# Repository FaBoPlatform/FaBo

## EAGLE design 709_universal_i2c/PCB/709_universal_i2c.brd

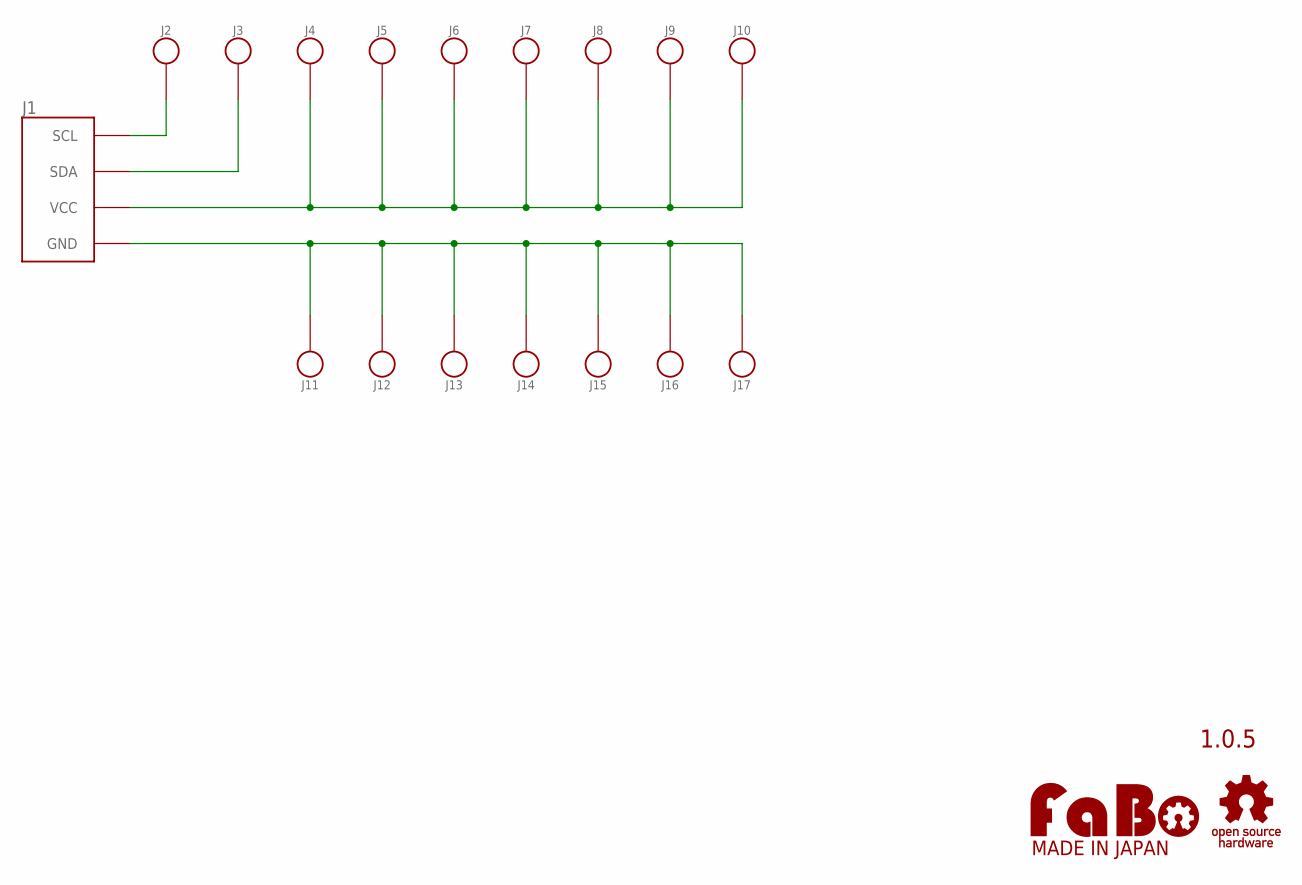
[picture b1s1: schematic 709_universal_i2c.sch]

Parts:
J1: FABO_BRICK_I2C-UNIVERSAL; FABO_BRICK_I2C_UNIVERSAL
J2, J3, J4, J5, J6, J7, J8, J9, J10, J11, J12, J13, J14, J15, J16, J17: PIN_HEADER_1X1_NOLABEL; PIN_1X1_NOLABEL
U$2: LOGO_OSHW-M_BOTTOM; LOGO_OSHW_M_BOTTOM
U$17: LOGO_FABO-M_BOTTOM; LOGO_FABO_MS_BOTTOM

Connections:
GND: J1.GND, J11.1, J12.1, J13.1, J14.1, J15.1, J16.1, J17.1
SCL: J1.SCL, J2.1
SDA: J1.SDA, J3.1
VCC: J1.VCC, J4.1, J5.1, J6.1, J7.1, J8.1, J9.1, J10.1

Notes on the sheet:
1.0.5

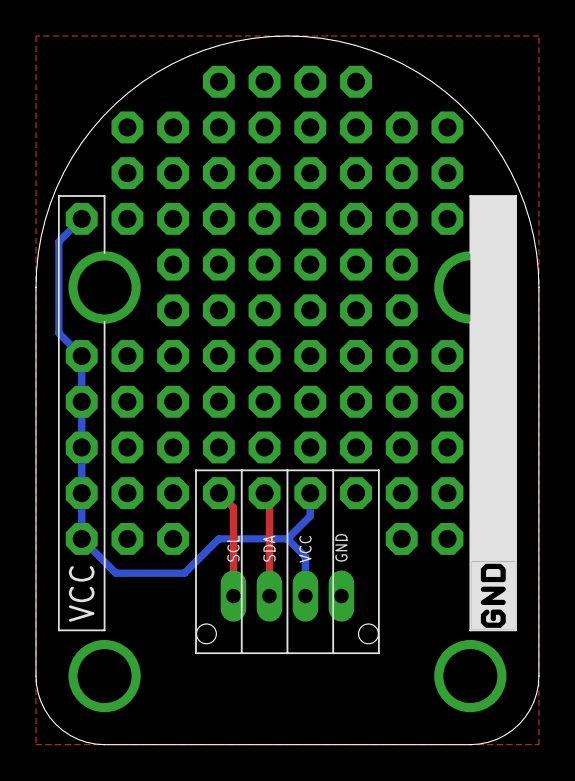
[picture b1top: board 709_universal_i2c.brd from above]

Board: 2 copper layers, 27.9 x 39.4 mm, 20 parts (0 on the bottom side), 4 nets.

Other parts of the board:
U$3: LOGO_SILK_GND

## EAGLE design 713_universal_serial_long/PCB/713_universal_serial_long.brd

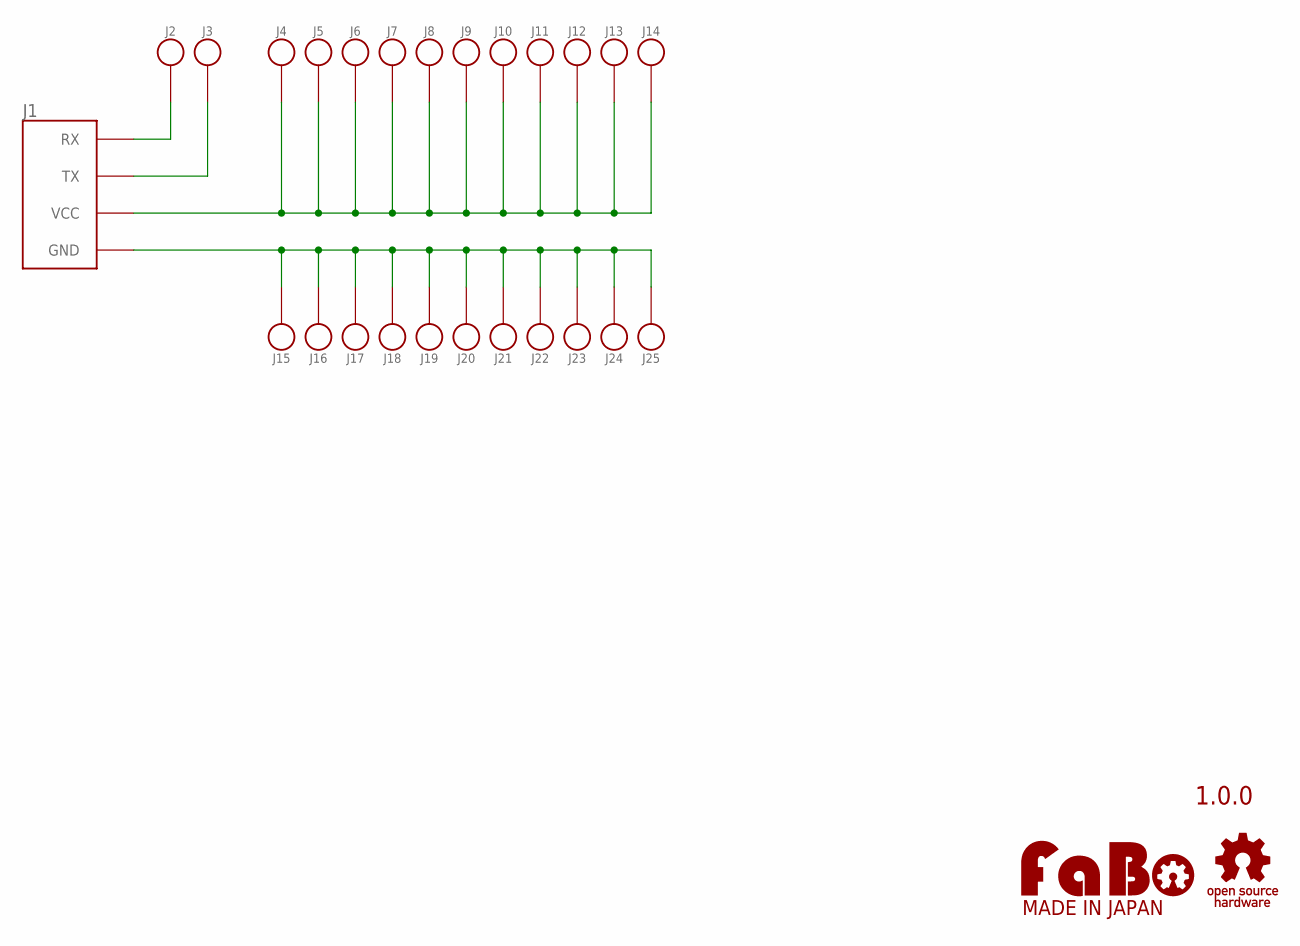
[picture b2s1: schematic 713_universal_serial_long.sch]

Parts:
J1: FABO_BRICK_SERIAL-UNIVERSAL_LONG; FABO_BRICK_SERIAL_UNIVERSAL_LONG
J2, J3, J4, J5, J6, J7, J8, J9, J10, J11, J12, J13, J14, J15, J16, J17, J18, J19, J20, J21, J22, J23, J24, J25: PIN_HEADER_1X1_NOLABEL; PIN_1X1_NOLABEL
U$2: LOGO_OSHW-M_BOTTOM; LOGO_OSHW_M_BOTTOM
U$3: LOGO_FABO-M; LOGO_FABO_MS

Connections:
GND: J1.GND, J15.1, J16.1, J17.1, J18.1, J19.1, J20.1, J21.1, J22.1, J23.1, J24.1, J25.1
RX: J1.RX, J2.1
TX: J1.TX, J3.1
VCC: J1.VCC, J4.1, J5.1, J6.1, J7.1, J8.1, J9.1, J10.1, J11.1, J12.1, J13.1, J14.1

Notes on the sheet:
1.0.0

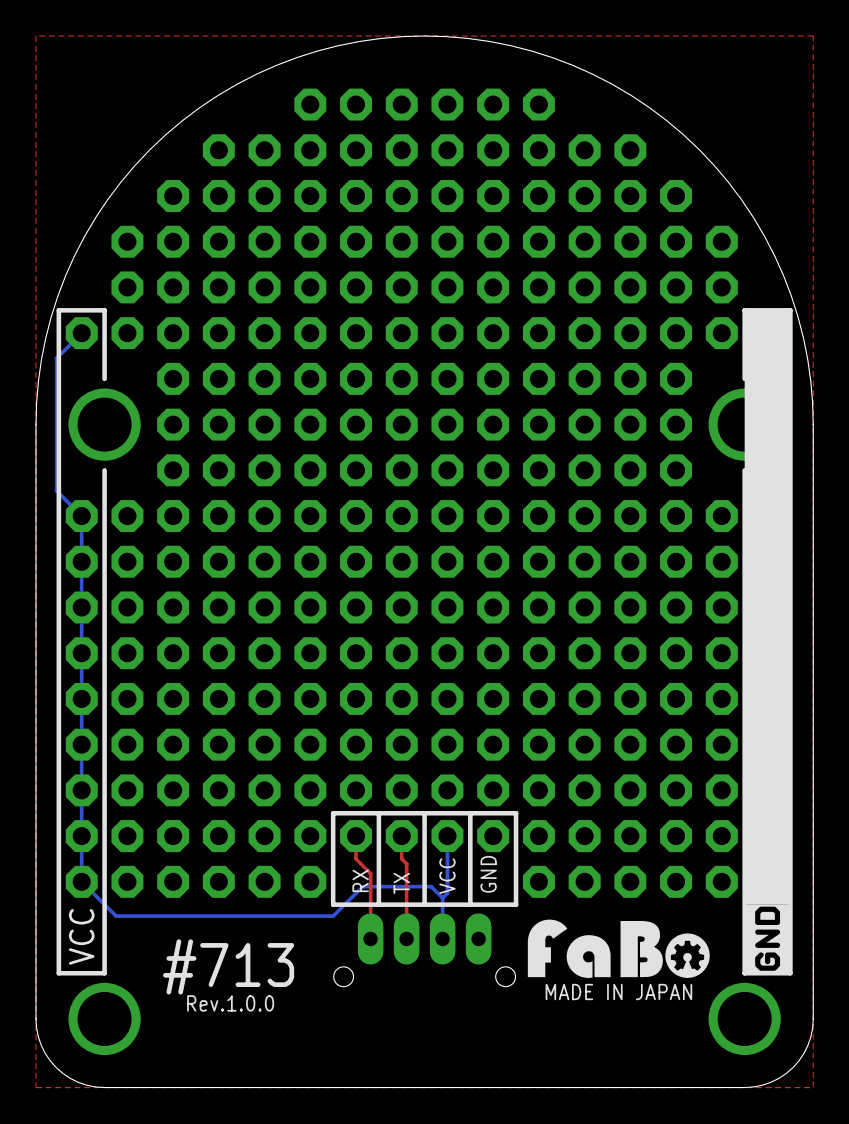
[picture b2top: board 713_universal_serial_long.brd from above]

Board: 2 copper layers, 43.2 x 58.4 mm, 28 parts (0 on the bottom side), 4 nets.

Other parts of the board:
U$4: LOGO_SILK_GND

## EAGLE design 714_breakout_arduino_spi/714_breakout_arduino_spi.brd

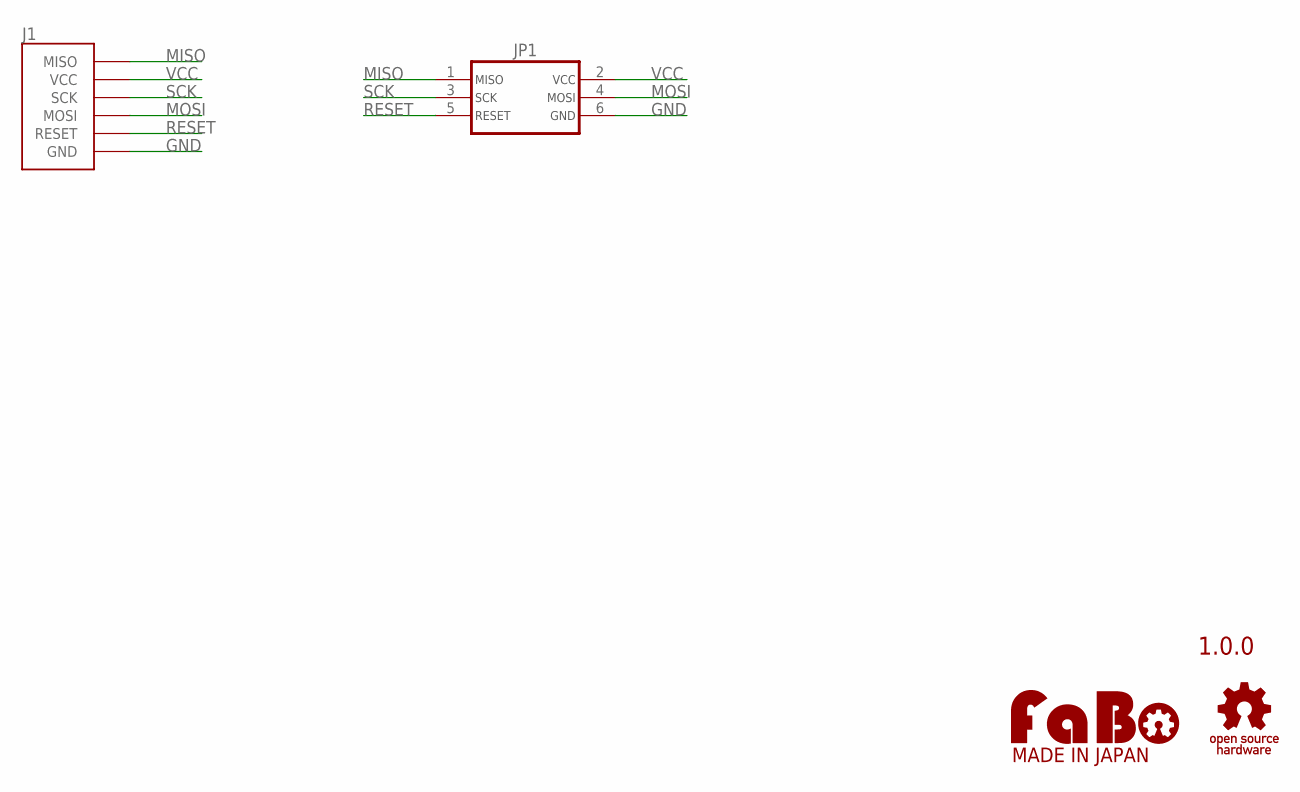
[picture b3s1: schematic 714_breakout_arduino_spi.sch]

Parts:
J1: FABO_BREAKOUT_ARDUINO_SPI
JP1: AVR_ISP-PTH; PIN_2X3
U$2: LOGO_OSHW-M_BOTTOM; LOGO_OSHW_M_BOTTOM
U$3: LOGO_FABO-M_BOTTOM; LOGO_FABO_MS_BOTTOM

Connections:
GND: J1.GND, JP1.6
MISO: J1.MISO, JP1.1
MOSI: J1.MOSI, JP1.4
RESET: J1.RESET, JP1.5
SCK: J1.SCK, JP1.3
VCC: J1.VCC, JP1.2

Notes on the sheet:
1.0.0

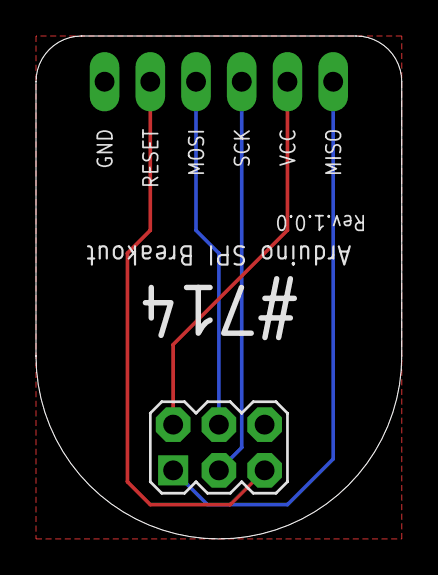
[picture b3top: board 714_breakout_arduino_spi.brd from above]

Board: 2 copper layers, 20.3 x 27.9 mm, 4 parts (0 on the bottom side), 6 nets.

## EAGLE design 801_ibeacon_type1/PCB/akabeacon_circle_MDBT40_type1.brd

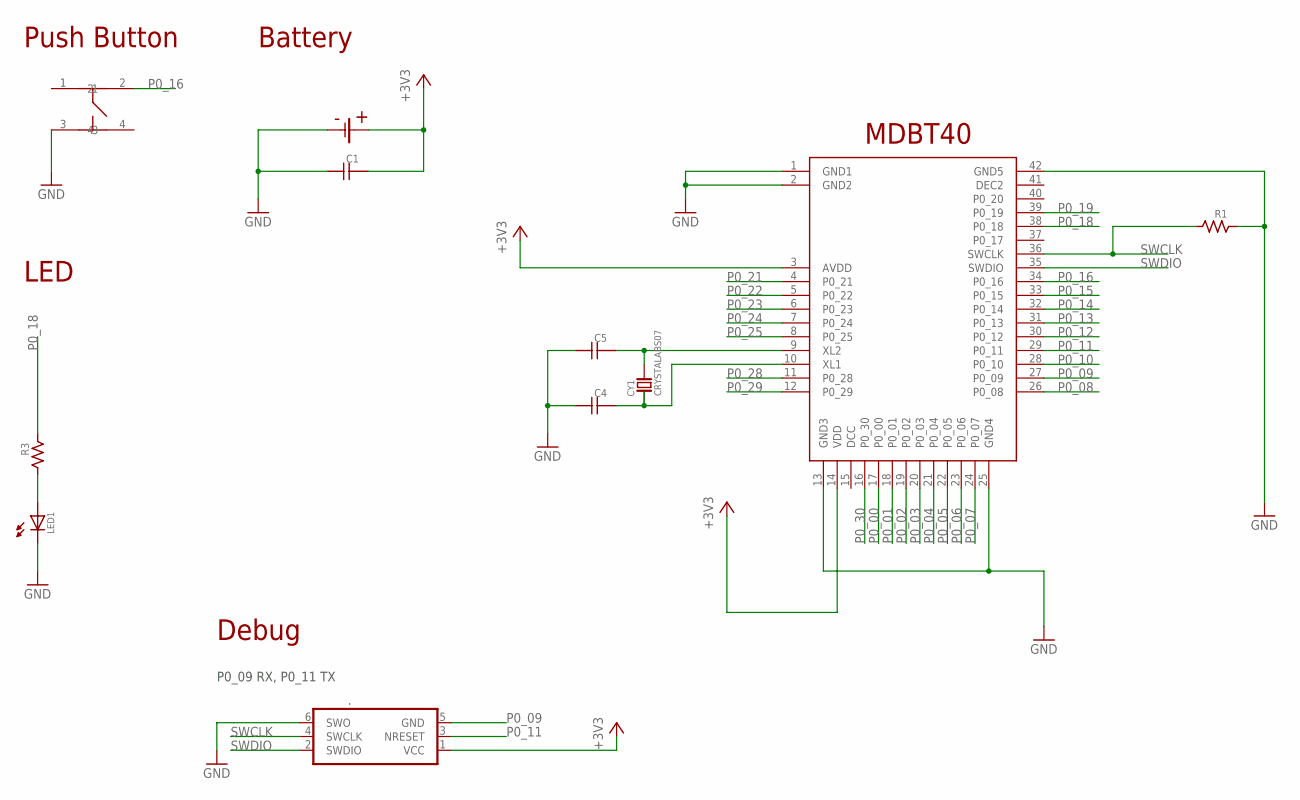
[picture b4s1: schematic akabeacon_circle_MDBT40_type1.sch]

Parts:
.: TC2030-IDC-NL
C1, C4, C5: CAPACITOR-0603; 0603
CY1: CRYSTALABS07; ABRACOM-ABS07-32.768KHZ
LED1: LED-0603; 0603
R1, R3: RESISTOR-0603; 0603
U$1: RAYTAC-MDBT40
U$2: CH031-2477LF
U$5: SWICTH-4P(KMR2); SWITCH-4P(KMR2)

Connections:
+3V3: ..1 (VCC), C1.2, U$1.3 (AVDD), U$1.14 (VDD), U$2.+
GND: ..6 (SWO), C1.1, C4.1, C5.1, LED1.CATHODE, R1.2, U$1.1 (GND1), U$1.2 (GND2), U$1.13 (GND3), U$1.25 (GND4), U$1.42 (GND5), U$2.-, U$5.3
unnamed: LED1.ANODE, R3.1
unnamed: C5.2, CY1.P$2, U$1.9 (XL2)
unnamed: C4.2, CY1.P$1, U$1.10 (XL1)
P0_00: U$1.17 (P0_00)
P0_01: U$1.18 (P0_01)
P0_02: U$1.19 (P0_02)
P0_03: U$1.20 (P0_03)
P0_04: U$1.21 (P0_04)
P0_05: U$1.22 (P0_05)
P0_06: U$1.23 (P0_06)
P0_07: U$1.24 (P0_07)
P0_08: U$1.26 (P0_08)
P0_09: ..5 (GND), U$1.27 (P0_09)
P0_10: U$1.28 (P0_10)
P0_11: ..3 (NRESET), U$1.29 (P0_11)
P0_12: U$1.30 (P0_12)
P0_13: U$1.31 (P0_13)
P0_14: U$1.32 (P0_14)
P0_15: U$1.33 (P0_15)
P0_16: U$1.34 (P0_16), U$5.2
P0_18: R3.2, U$1.38 (P0_18)
P0_19: U$1.39 (P0_19)
P0_21: U$1.4 (P0_21)
P0_22: U$1.5 (P0_22)
P0_23: U$1.6 (P0_23)
P0_24: U$1.7 (P0_24)
P0_25: U$1.8 (P0_25)
P0_28: U$1.11 (P0_28)
P0_29: U$1.12 (P0_29)
P0_30: U$1.16 (P0_30)
SWCLK: ..4 (SWCLK), R1.1, U$1.36 (SWCLK)
SWDIO: ..2 (SWDIO), U$1.35 (SWDIO)

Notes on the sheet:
Battery
Push Button
MDBT40
LED
Debug
P0_09 RX, P0_11 TX

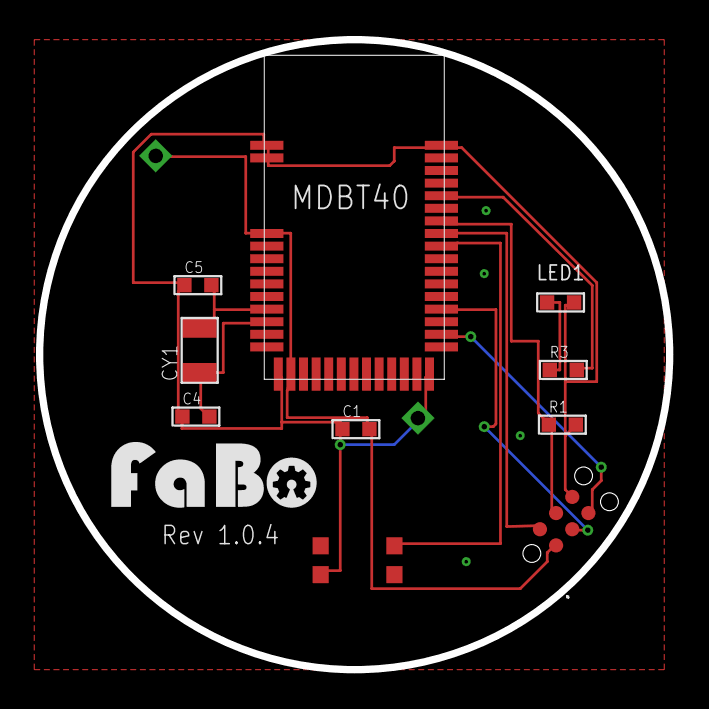
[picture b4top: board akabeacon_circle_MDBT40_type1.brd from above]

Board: 2 copper layers, 35.0 x 35.0 mm, 12 parts (0 on the bottom side), 11 nets.

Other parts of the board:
U$3: LOGO_FABO_M

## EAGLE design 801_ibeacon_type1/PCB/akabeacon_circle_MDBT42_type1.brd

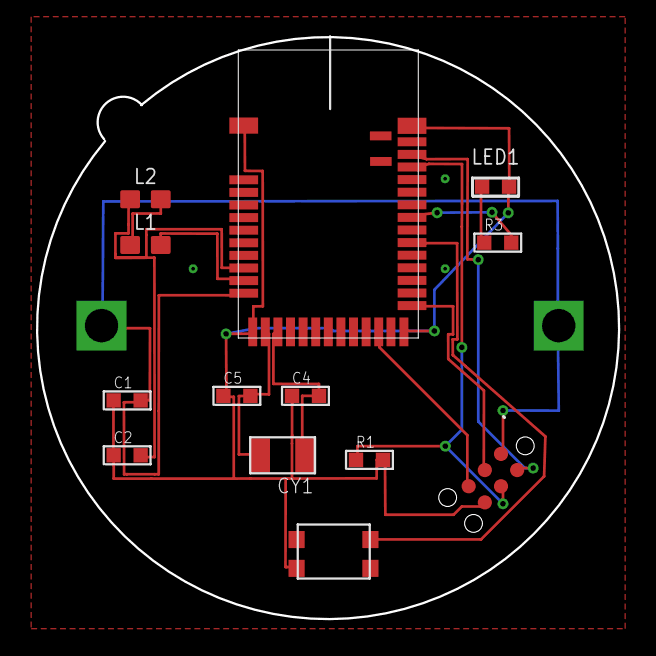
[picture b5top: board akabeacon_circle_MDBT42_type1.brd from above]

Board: 2 copper layers, 32.3 x 32.3 mm, 14 parts (0 on the bottom side), 14 nets.

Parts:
.: TC2030-IDC-NL
C1: 0603
C2: 1uf; 0603
C4: 12@f; 0603
C5: 12pf; 0603
CY1: CRYSTALABS07; ABRACOM-ABS07-32.768KHZ
L1: 10nh; 0603
L2: 15nh; 0603
LED1: 0603
R1, R3: 0603
U$2: RAYTAC-MDBT42
U$3: CIRCLE-TYPE2; CIRCLE-TYPE2-TC2030
U$5: SWICTH-4P(KMR2); SWITCH-4P(KMR2)

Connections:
+3V3: ..1, C1.2, U$2.11, U$3.P$1, U$3.P$2
DCC: L1.2, U$2.10
DEC4: C2.2, L2.1, U$2.9
GND: ..6, C1.1, C2.1, C4.1, C5.1, LED1.CATHODE, R1.2, U$2.1, U$2.12, U$2.24, U$2.39, U$3.GND, U$5.3
unnamed: LED1.ANODE, R3.1
unnamed: L1.1, L2.2
unnamed: C5.2, CY1.P$2, U$2.13
unnamed: C4.2, CY1.P$1, U$2.14
P0.09: ..5, U$2.22
P0.11: ..3, U$2.25
P0.16: U$2.30, U$5.2
P0.18: R3.2, U$2.32
SWCLK: ..4, R1.1, U$2.36
SWDIO: ..2, U$2.37

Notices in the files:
parts and their libraries:
FaBo-etc: Released under the Creative Commons Attribution-ShareAlike 4.0 License
https://creativecommons.org/licenses/by-sa/4.0
FaBo-etc: Released under the Creative Commons
SparkFun: Licensing: CC v3.0 Share-Alike You are welcome to use this library for commercial purposes.
